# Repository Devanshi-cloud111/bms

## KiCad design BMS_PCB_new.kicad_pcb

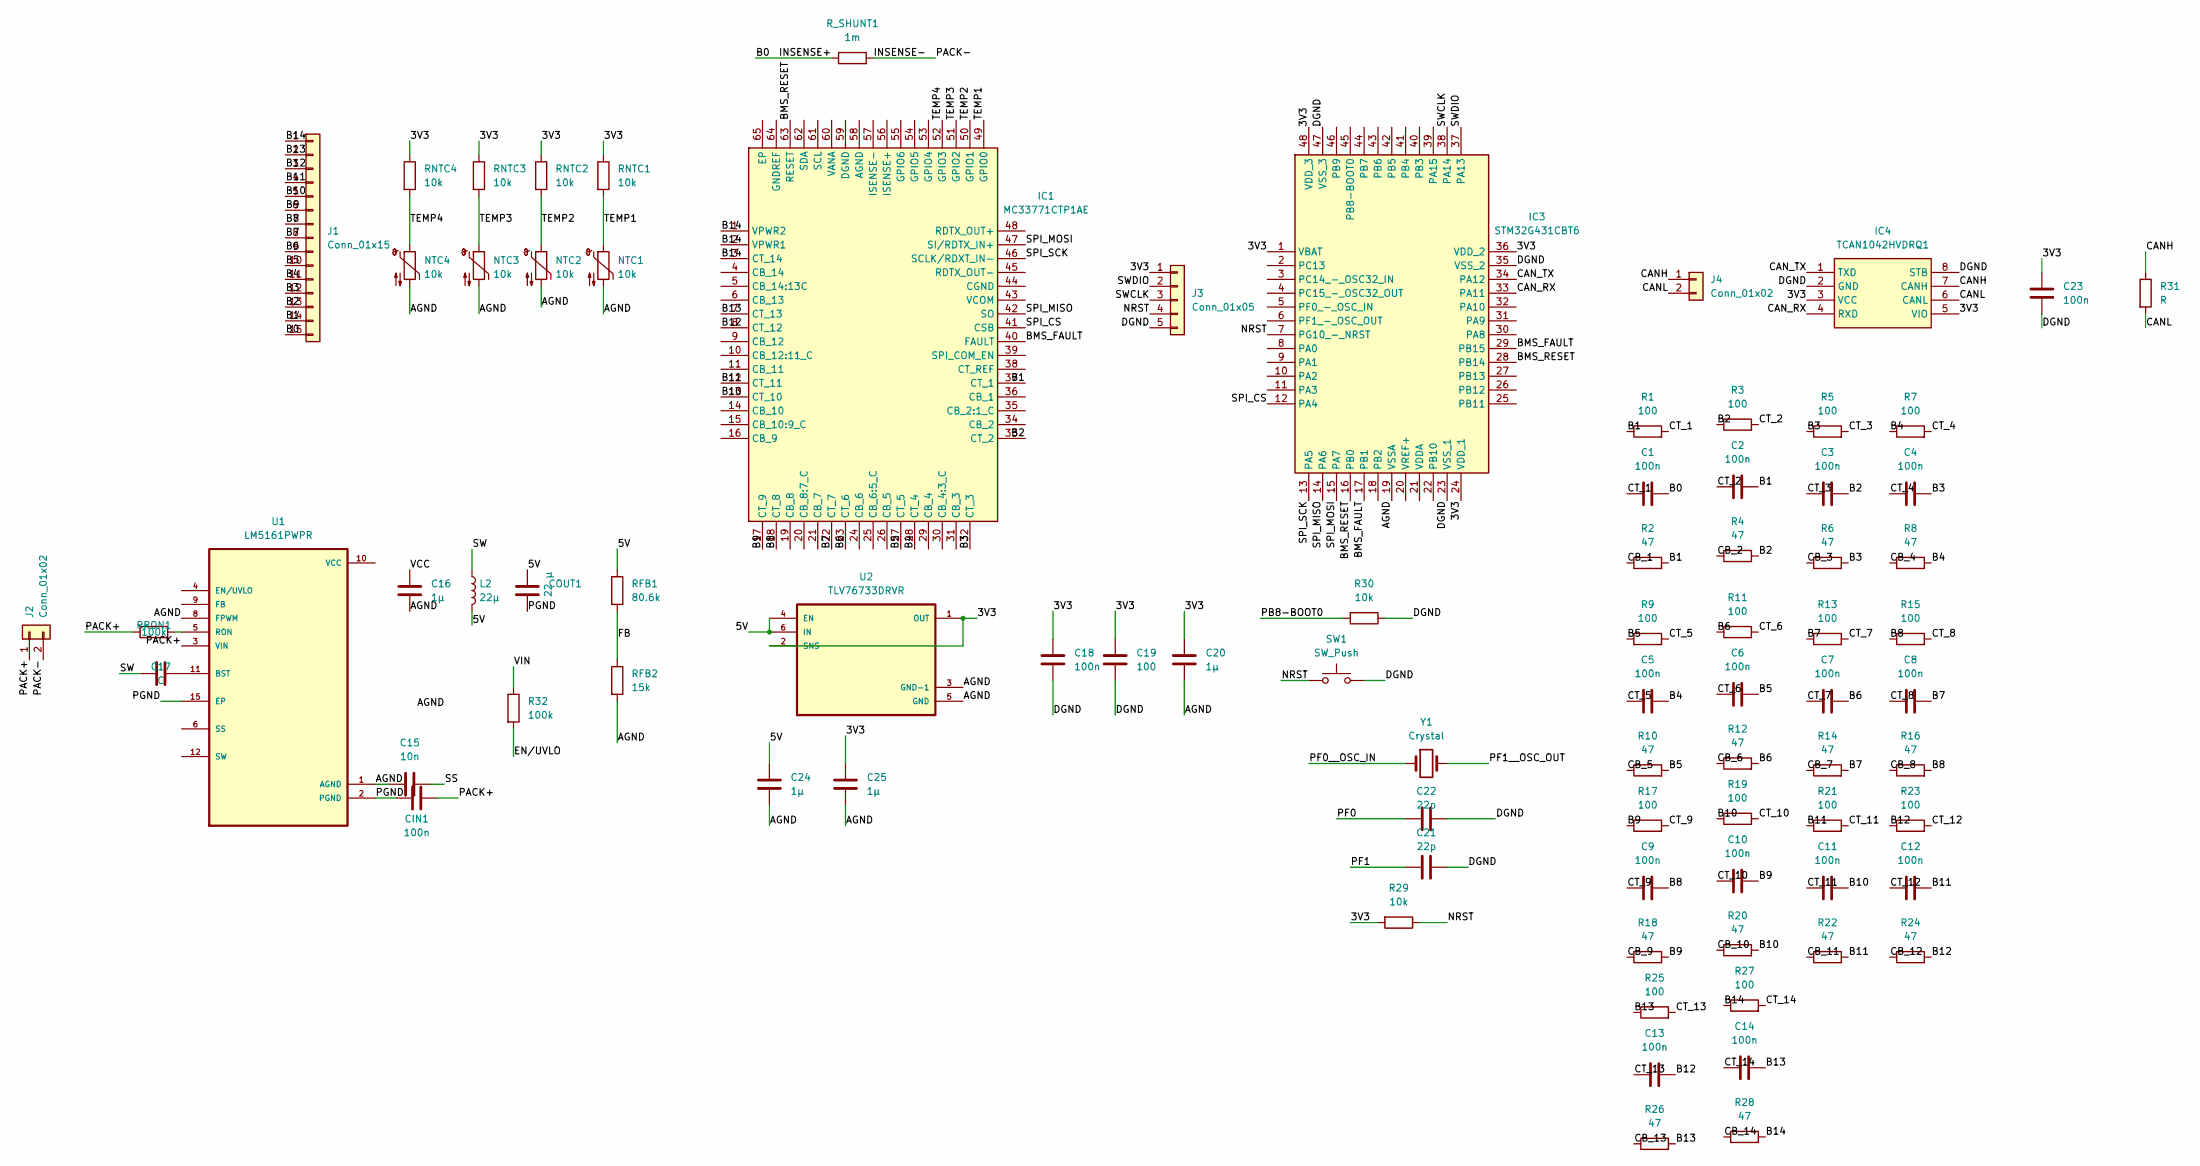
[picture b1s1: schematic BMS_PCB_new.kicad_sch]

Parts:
C1, C2, C3, C4, C5, C6, C7, C8, C9, C10, C11, C12, C13, C14, C18, C23: 100n; C_0603_1608Metric
C15: 10n; C_0603_1608Metric
C16, C20, C24, C25: 1µ; C_0603_1608Metric
C17: C; C_0603_1608Metric
C19: 100; C_0603_1608Metric
C21, C22: 22p; C_0603_1608Metric
CIN1: 100n; C_0603_1608Metric
COUT1: 22 µ; C_0603_1608Metric
IC1: MC33771CTP1AE; LQFP-64_14x14mm_P0.8mm; Manufacturer_Part_Number MC33771CTP1AE; Mouser Part Number 771-MC33771CTP1AE
IC3: STM32G431CBT6; LQFP-48_7x7mm_P0.5mm; Manufacturer_Part_Number STM32G431CBT6; Mouser Part Number 511-STM32G431CBT6
IC4: TCAN1042HVDRQ1; SOIC-8-N7_3.9x4.9mm_P1.27mm; Manufacturer_Part_Number TCAN1042HVDRQ1; Mouser Part Number 595-TCAN1042HVDRQ1
J1: Conn_01x15; PinHeader_1x15_P2.54mm_Vertical
J2, J4: Conn_01x02; PinHeader_1x02_P2.54mm_Vertical
J3: Conn_01x05; PinHeader_1x05_P2.54mm_Vertical
L2: 22µ; L_Coilcraft_XAL6020-XXX
NTC1, NTC2, NTC3, NTC4: 10k; R_0805_2012Metric
R1, R3, R5, R7, R9, R11, R13, R15, R17, R19, R21, R23, R25, R27: 100; R_0805_2012Metric
R2: 47; L_Taiyo-Yuden_NR-60xx
R4, R6, R8, R10, R12, R14, R16, R18, R20, R22, R24, R26, R28: 47; R_0805_2012Metric
R29, R30: 10k; R_0805_2012Metric
R31: R; R_0805_2012Metric
R32: 100k; R_0805_2012Metric
RFB1: 80.6k; R_0805_2012Metric
RFB2: 15k; R_0805_2012Metric
RNTC1, RNTC2, RNTC3, RNTC4: 10k; R_0805_2012Metric
RRON1: 100k; R_0805_2012Metric
R_SHUNT1: 1m; R_0805_2012Metric
SW1: SW_Push; SW_Push_1P1T_NO_CK_KMR2
U1: LM5161PWPR; Texas_HTSSOP-14-1EP_4.4x5mm_P0.65mm_EP3.4x5mm_Mask3.155x3.2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
U2: TLV76733DRVR; DFN-6-1EP_2x2mm_P0.65mm_EP1.01x1.7mm
Y1: Crystal; Crystal_SMD_3225-4Pin_3.2x2.5mm

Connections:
/3V3: C18.1, C19.1, C20.1, C23.1, C25.1, IC3.1 (VBAT), IC3.24 (VDD_1), IC3.36 (VDD_2), IC3.48 (VDD_3), IC4.3 (VCC), IC4.5 (VIO), J3.1, R29.2, RNTC1.1, RNTC2.1, RNTC3.1, RNTC4.1, U2.1 (OUT), U2.2 (SNS)
/5V: C24.1, COUT1.1, L2.2, RFB1.1, U2.4 (EN), U2.6 (IN)
/AGND: C15.1, C16.2, C20.2, C24.2, C25.2, IC3.19 (VSSA), NTC1.2, NTC2.2, NTC3.2, NTC4.2, RFB2.2, U1.1 (AGND), U1.8 (FPWM), U2.3 (GND-1), U2.5 (GND)
/B0: C1.2, J1.15, R_SHUNT1.1
/B1: C2.2, IC1.37 (CT_1), J1.14, R1.1, R2.2
/B2: C3.2, IC1.33 (CT_2), J1.13, R3.1, R4.2
/B3: C4.2, IC1.32 (CT_3), J1.12, R5.1, R6.2
/B4: C5.2, IC1.28 (CT_4), J1.11, R7.1, R8.2
/B5: C6.2, IC1.27 (CT_5), J1.10, R9.1, R10.2
/B6: C7.2, IC1.23 (CT_6), J1.9, R11.1, R12.2
/B7: C8.2, IC1.22 (CT_7), J1.8, R13.1, R14.2
/B8: C9.2, IC1.18 (CT_8), J1.7, R15.1, R16.2
/B9: C10.2, IC1.17 (CT_9), J1.6, R17.1, R18.2
/B10: C11.2, IC1.13 (CT_10), J1.5, R19.1, R20.2
/B11: C12.2, IC1.12 (CT_11), J1.4, R21.1, R22.2
/B12: C13.2, IC1.8 (CT_12), J1.3, R23.1, R24.2
/B13: C14.2, IC1.7 (CT_13), J1.2, R25.1, R26.2
/B14: IC1.1 (VPWR2), IC1.2 (VPWR1), IC1.3 (CT_14), J1.1, R27.1, R28.2
/BMS_FAULT: IC1.40 (FAULT), IC3.17 (PB1), IC3.29 (PB15)
/BMS_RESET: IC1.63 (RESET), IC3.16 (PB0), IC3.28 (PB14)
/CANH: IC4.7 (CANH), J4.1, R31.1
/CANL: IC4.6 (CANL), J4.2, R31.2
/CAN_RX: IC3.33 (PA11), IC4.4 (RXD)
/CAN_TX: IC3.34 (PA12), IC4.1 (TXD)
/CB_1: R2.1
/CB_2: R4.1
/CB_3: R6.1
/CB_4: R8.1
/CB_5: R10.1
/CB_6: R12.1
/CB_7: R14.1
/CB_8: R16.1
/CB_9: R18.1
/CB_10: R20.1
/CB_11: R22.1
/CB_12: R24.1
/CB_13: R26.1
/CB_14: R28.1
/CT_1: C1.1, R1.2
/CT_2: C2.1, R3.2
/CT_3: C3.1, R5.2
/CT_4: C4.1, R7.2
/CT_5: C5.1, R9.2
/CT_6: C6.1, R11.2
/CT_7: C7.1, R13.2
/CT_8: C8.1, R15.2
/CT_9: C9.1, R17.2
/CT_10: C10.1, R19.2
/CT_11: C11.1, R21.2
/CT_13: C13.1, R25.2
/CT_14: C14.1, R27.2
/DGND: C18.2, C19.2, C21.2, C22.2, C23.2, IC3.23 (VSS_1), IC3.35 (VSS_2), IC3.47 (VSS_3), IC4.2 (GND), IC4.8 (STB), J3.5, R30.1, SW1.2
/FB: RFB1.2, RFB2.1
/INSENSE-: J2.2, R_SHUNT1.2
/NRST: IC3.7 (PG10_-_NRST), J3.4, R29.1, SW1.1
/PACK+: CIN1.2, J2.1, RRON1.1, U1.3 (VIN)
/PB8-BOOT0: R30.2
/PF0: C22.1
/PF0__OSC_IN: Y1.1
/PF1: C21.1
/PF1__OSC_OUT: Y1.2
/PGND: CIN1.1, COUT1.2, U1.2 (PGND), U1.15 (EP)
/SPI_CS: IC1.41 (CSB), IC3.12 (PA4)
/SPI_MISO: IC1.42 (SO), IC3.14 (PA6)
/SPI_MOSI: IC1.47 (SI/RDTX_IN+), IC3.15 (PA7)
/SPI_SCK: IC1.46 (SCLK/RDXT_IN-), IC3.13 (PA5)
/SS: C15.2
/SW: C17.2, L2.1
/SWCLK: IC3.38 (PA14), J3.3
/SWDIO: IC3.37 (PA13), J3.2
/TEMP1: IC1.49 (GPIO0), NTC1.1, RNTC1.2
/TEMP2: IC1.50 (GPIO1), NTC2.1, RNTC2.2
/TEMP3: IC1.51 (GPIO2), NTC3.1, RNTC3.2
/TEMP4: IC1.52 (GPIO3), NTC4.1, RNTC4.2
/VCC: C16.1
GND: C12.1, R23.2
unnamed: C17.1, U1.11 (BST)
unnamed: RRON1.2, U1.5 (RON)
unnamed: U1.12 (SW), U1.13 (SW)

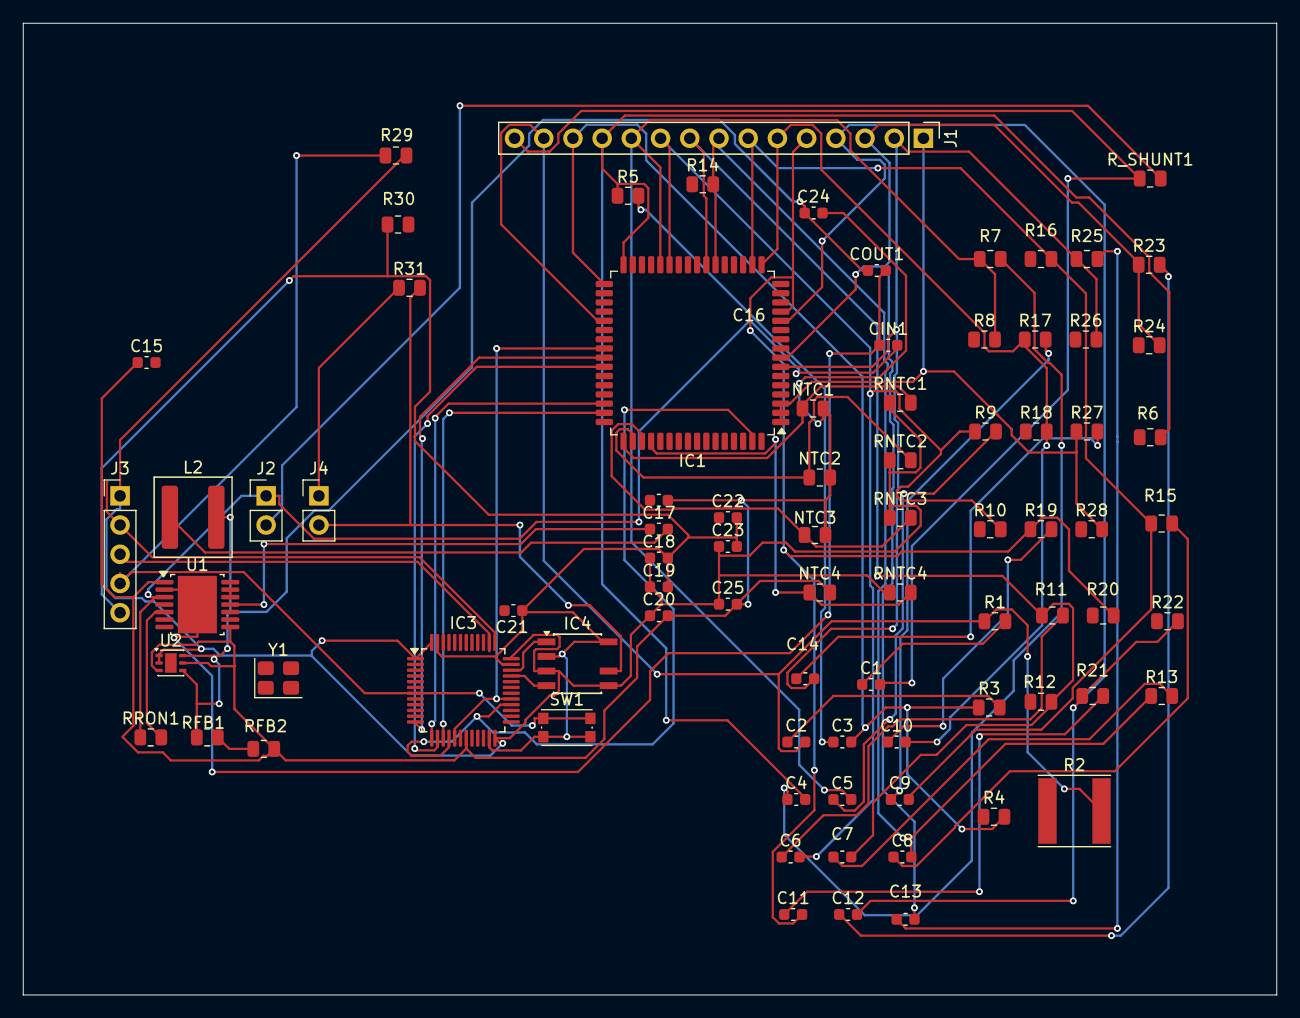
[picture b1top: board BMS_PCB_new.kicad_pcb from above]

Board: 2 copper layers, 109.0 x 84.5 mm, 82 parts (0 on the bottom side), 58 nets.
